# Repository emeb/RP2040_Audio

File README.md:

# RP2040_Audio
A Eurorack module for stereo audio effects based on the Raspberry Pi RP2040 MCU

## Abstract
I've been doing audio synthesis and effects in the Eurorack modular market for
a number of years. I started out in the late 2000's using the Microchip dsPIC
and migrated over to ARM Cortex M devices, mostly STM32 in order to get access
to higher speeds, more memory and floating point math. This was my main
platform for most of the 2010's until the great silicon drought of the 2020's
made high-end STM32 devices almost impossible to get. Into the vacuum stepped
the good folks at the Raspberry Pi Foundation with the RP2040 MCU which has
a fair chunk of on-chip SRAM, dual ARM Cortex M0 cores and a decent complement
of peripherals.

This project is a feasibility study of using the RP2040 MCU as an audio effects
processor, with particular emphasis on performance with challenging DSP.

## Hardware
The complete design consists of two PCBs:
* The system PCB - a single board containg all electrical components. Find it
in the Hardware directory.
* The Front Panel - a PCB-based front panel that conforms to the Eurorack
physical mounting standard. Found in the Hardware/audio_panel directory.

The system PCB has the following features:
* Standard Eurorack 16-pin shrouded power connector
* Two +/-5V CV inputs and associated analog signal conditioning 
* Two +/-7V Audio inputs and associated analog signal conditioning 
* Two +/-7V Audio outputs and associated analog drivers
* WM8731 stereo audio codec
* RP2040 and 4MB SPI flash with USB, SWD and serial interfaces for development
* 160 x 80 IPS LCD
* UI button

## Firmware
A demonstration firmware is included that exercises all of the capabilities of
the system, including the LCD, UI button, CV inputs and stereo audio I/O. It is
a basic multi-effects unit that supports a complement of audio DSP algorithms
that are easily extended by adding standardized modules to a data structure.
As provided here just three algorithms are available:
* Simple pass-thru with no processing
* Simple gain control
* Basic "clean delay" with crossfaded deglitching during delay changes.

Other algorithms have been tested including phasers, flangers, frequency shifters,
resampling delays and reverbs, but these are not publicly released at this time.

## Findings
Overall the RP2040 is a capable device that can do a reasonable amount of audio
DSP. The lack of floating point is not a huge incovenience if one is handy with
fixed point arithmetic and the large on-chip SRAM is sufficiently large for
reasonable audio data buffers. The PIO is handy for building interfaces and is
capable of full-duplex I2S with no difficulty. The on-chip ADC underperforms its
12-bit data width however and requires a fair bit of post-processing to remove
noise and jitter in the conversion results. The dual ARM cores are useful in
dividing up user interface and DSP tasks to keep a snappy response, but even
with two cores the system struggles to compete with higher-spec ARM systems.

TL;DR - you can use it for DSP, but I'd prefer a Cortex M7.

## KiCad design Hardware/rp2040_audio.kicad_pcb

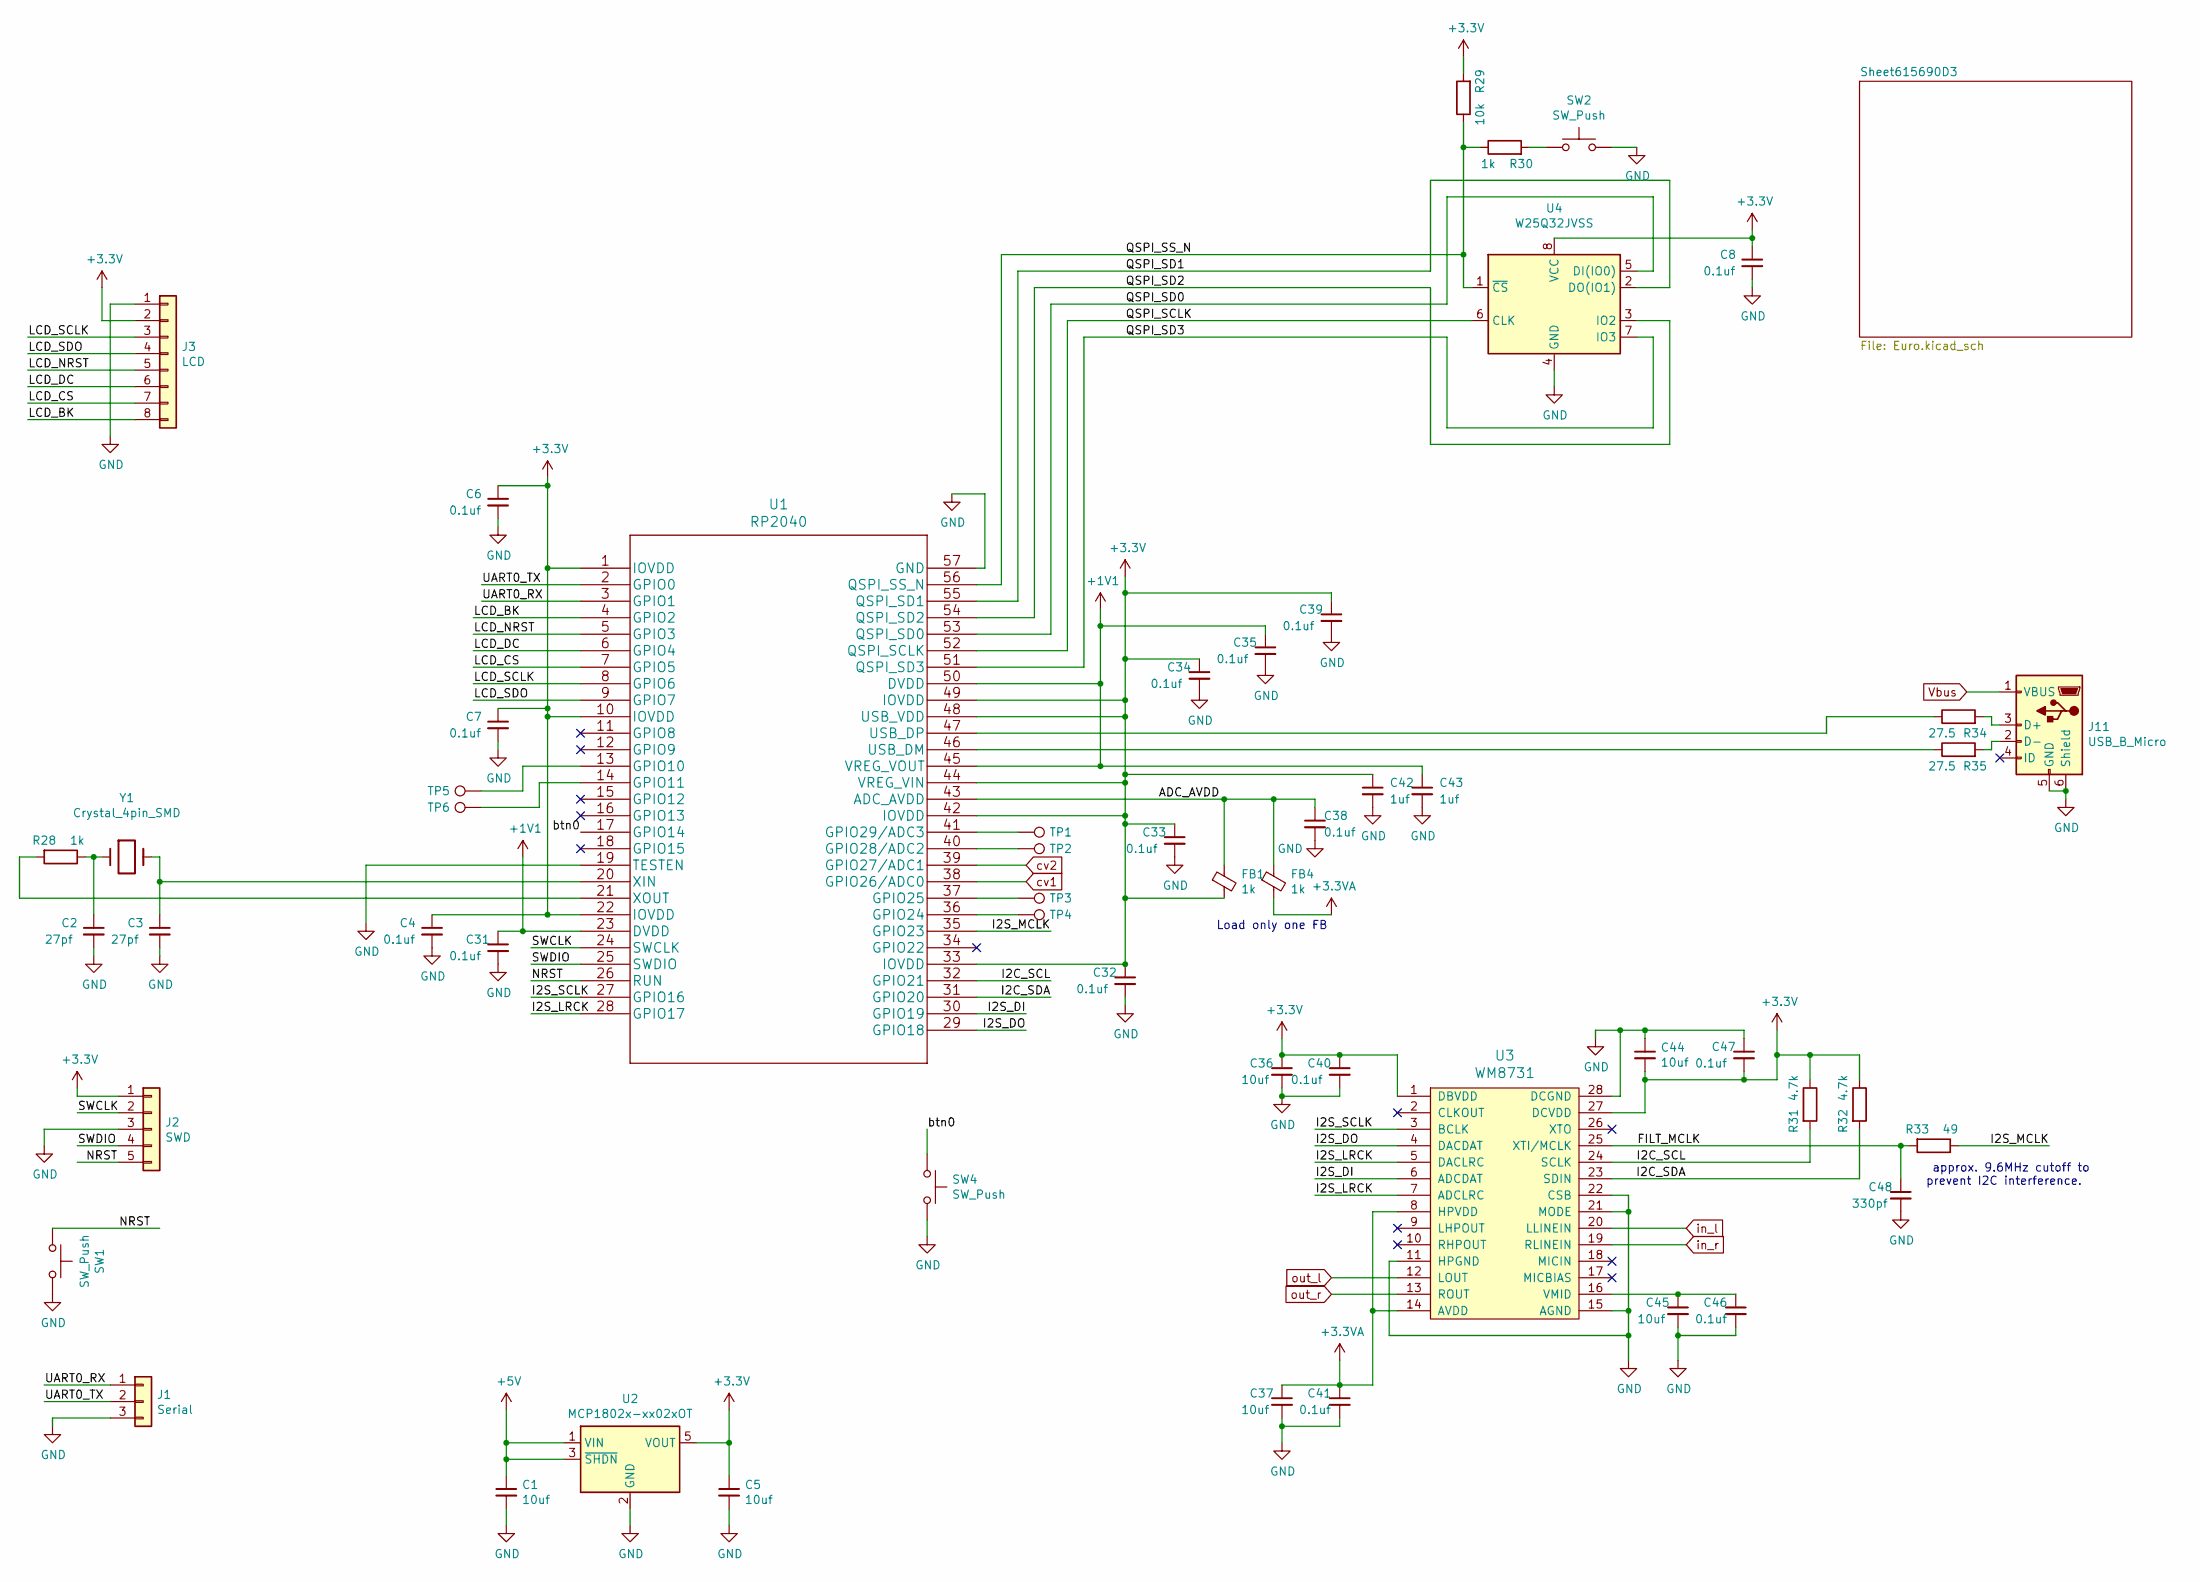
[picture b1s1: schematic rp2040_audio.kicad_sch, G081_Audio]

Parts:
C1, C5, C36, C37, C44, C45: 10uf; C_0805
C2, C3: 27pf; C_0603
C4, C6, C7, C8, C31, C32, C33, C34, C35, C38, C39, C40, C41, C46, C47: 0.1uf; C_0603
C42, C43: 1uf; C_0603
C48: 330pf; C_0603
FB1, FB4: 1k; C_0603
J1: Serial; Pin_Header_Straight_1x03_Pitch2.54mm
J2: SWD; Pin_Header_Straight_1x05_Pitch2.54mm
J3: LCD; LCD_80x160_0.96
J11: USB_B_Micro; USB_Micro-B_10103594-0001LF_actual_outline
R28, R30: 1k; R_0603
R29: 10k; R_0603
R31, R32: 4.7k; R_0603
R33: 49; R_0603
R34, R35: 27.5; R_0603
SW1, SW2: SW_Push; SW_SPST_KMR2
SW4: SW_Push; SW_PUSH_6mm_Center
TP1, TP2, TP3, TP4, TP5, TP6: TestPoint; Measurement_Point_Round-SMD-Pad_Small
U1: RP2040
U2: MCP1802x-xx02xOT; SOT-23-5
U3: WM8731; SSOP-28_5.3x10.2mm_Pitch0.65mm
U4: W25Q32JVSS; SOIC-8_5.23x5.23mm_P1.27mm
Y1: Crystal_4pin_SMD; Crystal_SMD_3225-4pin_3.2x2.5mm

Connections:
+1V1: C31.1, C35.1, C43.1, U1.23 (DVDD), U1.45 (VREG_VOUT), U1.50 (DVDD)
+3.3VA: C37.1, C41.1, FB4.2, U3.8 (HPVDD), U3.14 (AVDD); also elsewhere on the board
+3V3: C4.1, C5.1, C6.1, C7.1, C8.1, C32.1, C33.1, C34.1, C36.1, C39.1, C40.1, C42.1, C44.2, C47.2, FB1.2, J2.1, J3.2, R29.2, R31.1, R32.1, U1.1 (IOVDD), U1.10 (IOVDD), U1.22 (IOVDD), U1.33 (IOVDD), U1.42 (IOVDD), U1.44 (VREG_VIN), U1.48 (USB_VDD), U1.49 (IOVDD), U2.5 (VOUT), U3.1 (DBVDD), U3.27 (DCVDD), U4.8 (VCC)
+5V: C1.1, U2.1 (VIN), U2.3 (~SHDN); also elsewhere on the board
/ADC_AVDD: C38.1, FB1.1, FB4.1, U1.43 (ADC_AVDD)
/FILT_MCLK: C48.1, R33.2, U3.25 (XTI/MCLK)
/I2C_SCL: R31.2, U1.32 (GPIO21), U3.24 (SCLK)
/I2C_SDA: R32.2, U1.31 (GPIO20), U3.23 (SDIN)
/I2S_DI: U1.30 (GPIO19), U3.6 (ADCDAT)
/I2S_DO: U1.29 (GPIO18), U3.4 (DACDAT)
/I2S_LRCK: U1.28 (GPIO17), U3.5 (DACLRC), U3.7 (ADCLRC)
/I2S_MCLK: R33.1, U1.35 (GPIO23)
/I2S_SCLK: U1.27 (GPIO16), U3.3 (BCLK)
/LCD_BK: J3.8, U1.4 (GPIO2)
/LCD_CS: J3.7, U1.7 (GPIO5)
/LCD_DC: J3.6, U1.6 (GPIO4)
/LCD_NRST: J3.5, U1.5 (GPIO3)
/LCD_SCLK: J3.3, U1.8 (GPIO6)
/LCD_SDO: J3.4, U1.9 (GPIO7)
/NRST: J2.5, SW1.1, U1.26 (RUN)
/QSPI_SCLK: U1.52 (QSPI_SCLK), U4.6 (CLK)
/QSPI_SD0: U1.53 (QSPI_SD0), U4.5 (DI(IO0))
/QSPI_SD1: U1.55 (QSPI_SD1), U4.2 (DO(IO1))
/QSPI_SD2: U1.54 (QSPI_SD2), U4.3 (IO2)
/QSPI_SD3: U1.51 (QSPI_SD3), U4.7 (IO3)
/QSPI_SS_N: R29.1, R30.1, U1.56 (QSPI_SS_N), U4.1 (~CS)
/SWCLK: J2.2, U1.24 (SWCLK)
/SWDIO: J2.4, U1.25 (SWDIO)
/UART0_RX: J1.1, U1.3 (GPIO1)
/UART0_TX: J1.2, U1.2 (GPIO0)
/btn0: SW4.1, U1.17 (GPIO14)
GND: C1.2, C2.2, C3.2, C4.2, C5.2, C6.2, C7.2, C8.2, C31.2, C32.2, C33.2, C34.2, C35.2, C36.2, C37.2, C38.2, C39.2, C40.2, C41.2, C42.2, C43.2, C44.1, C45.2, C46.2, C47.1, C48.2, J1.3, J2.3, J3.1, J11.5 (GND), J11.6 (Shield), SW1.2, SW2.2, SW4.2, U1.19 (TESTEN), U1.57 (GND), U2.2 (GND), U3.11 (HPGND), U3.15 (AGND), U3.21 (MODE), U3.22 (CSB), U3.28 (DCGND), U4.4 (GND); also elsewhere on the board
unnamed: C2.1, R28.1, Y1.1
unnamed: C3.1, U1.20 (XIN), Y1.3
unnamed: C45.1, C46.1, U3.16 (VMID)
unnamed: J11.2 (D-), R35.2
unnamed: J11.3 (D+), R34.2
unnamed: R28.2, U1.21 (XOUT)
unnamed: R30.2, SW2.1
unnamed: R34.1, U1.47 (USB_DP)
unnamed: R35.1, U1.46 (USB_DM)
unnamed: TP1.1, U1.41 (GPIO29/ADC3)
unnamed: TP2.1, U1.40 (GPIO28/ADC2)
unnamed: TP3.1, U1.37 (GPIO25)
unnamed: TP4.1, U1.36 (GPIO24)
unnamed: TP5.1, U1.13 (GPIO10)
unnamed: TP6.1, U1.14 (GPIO11)
Vbus: J11.1 (VBUS); also elsewhere on the board
cv1: U1.38 (GPIO26/ADC0); also elsewhere on the board
cv2: U1.39 (GPIO27/ADC1); also elsewhere on the board
in_l: U3.20 (LLINEIN); also elsewhere on the board
in_r: U3.19 (RLINEIN); also elsewhere on the board
out_l: U3.12 (LOUT); also elsewhere on the board
out_r: U3.13 (ROUT); also elsewhere on the board

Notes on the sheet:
approx. 9.6MHz cutoff to prevent I2C interference.
Load only one FB

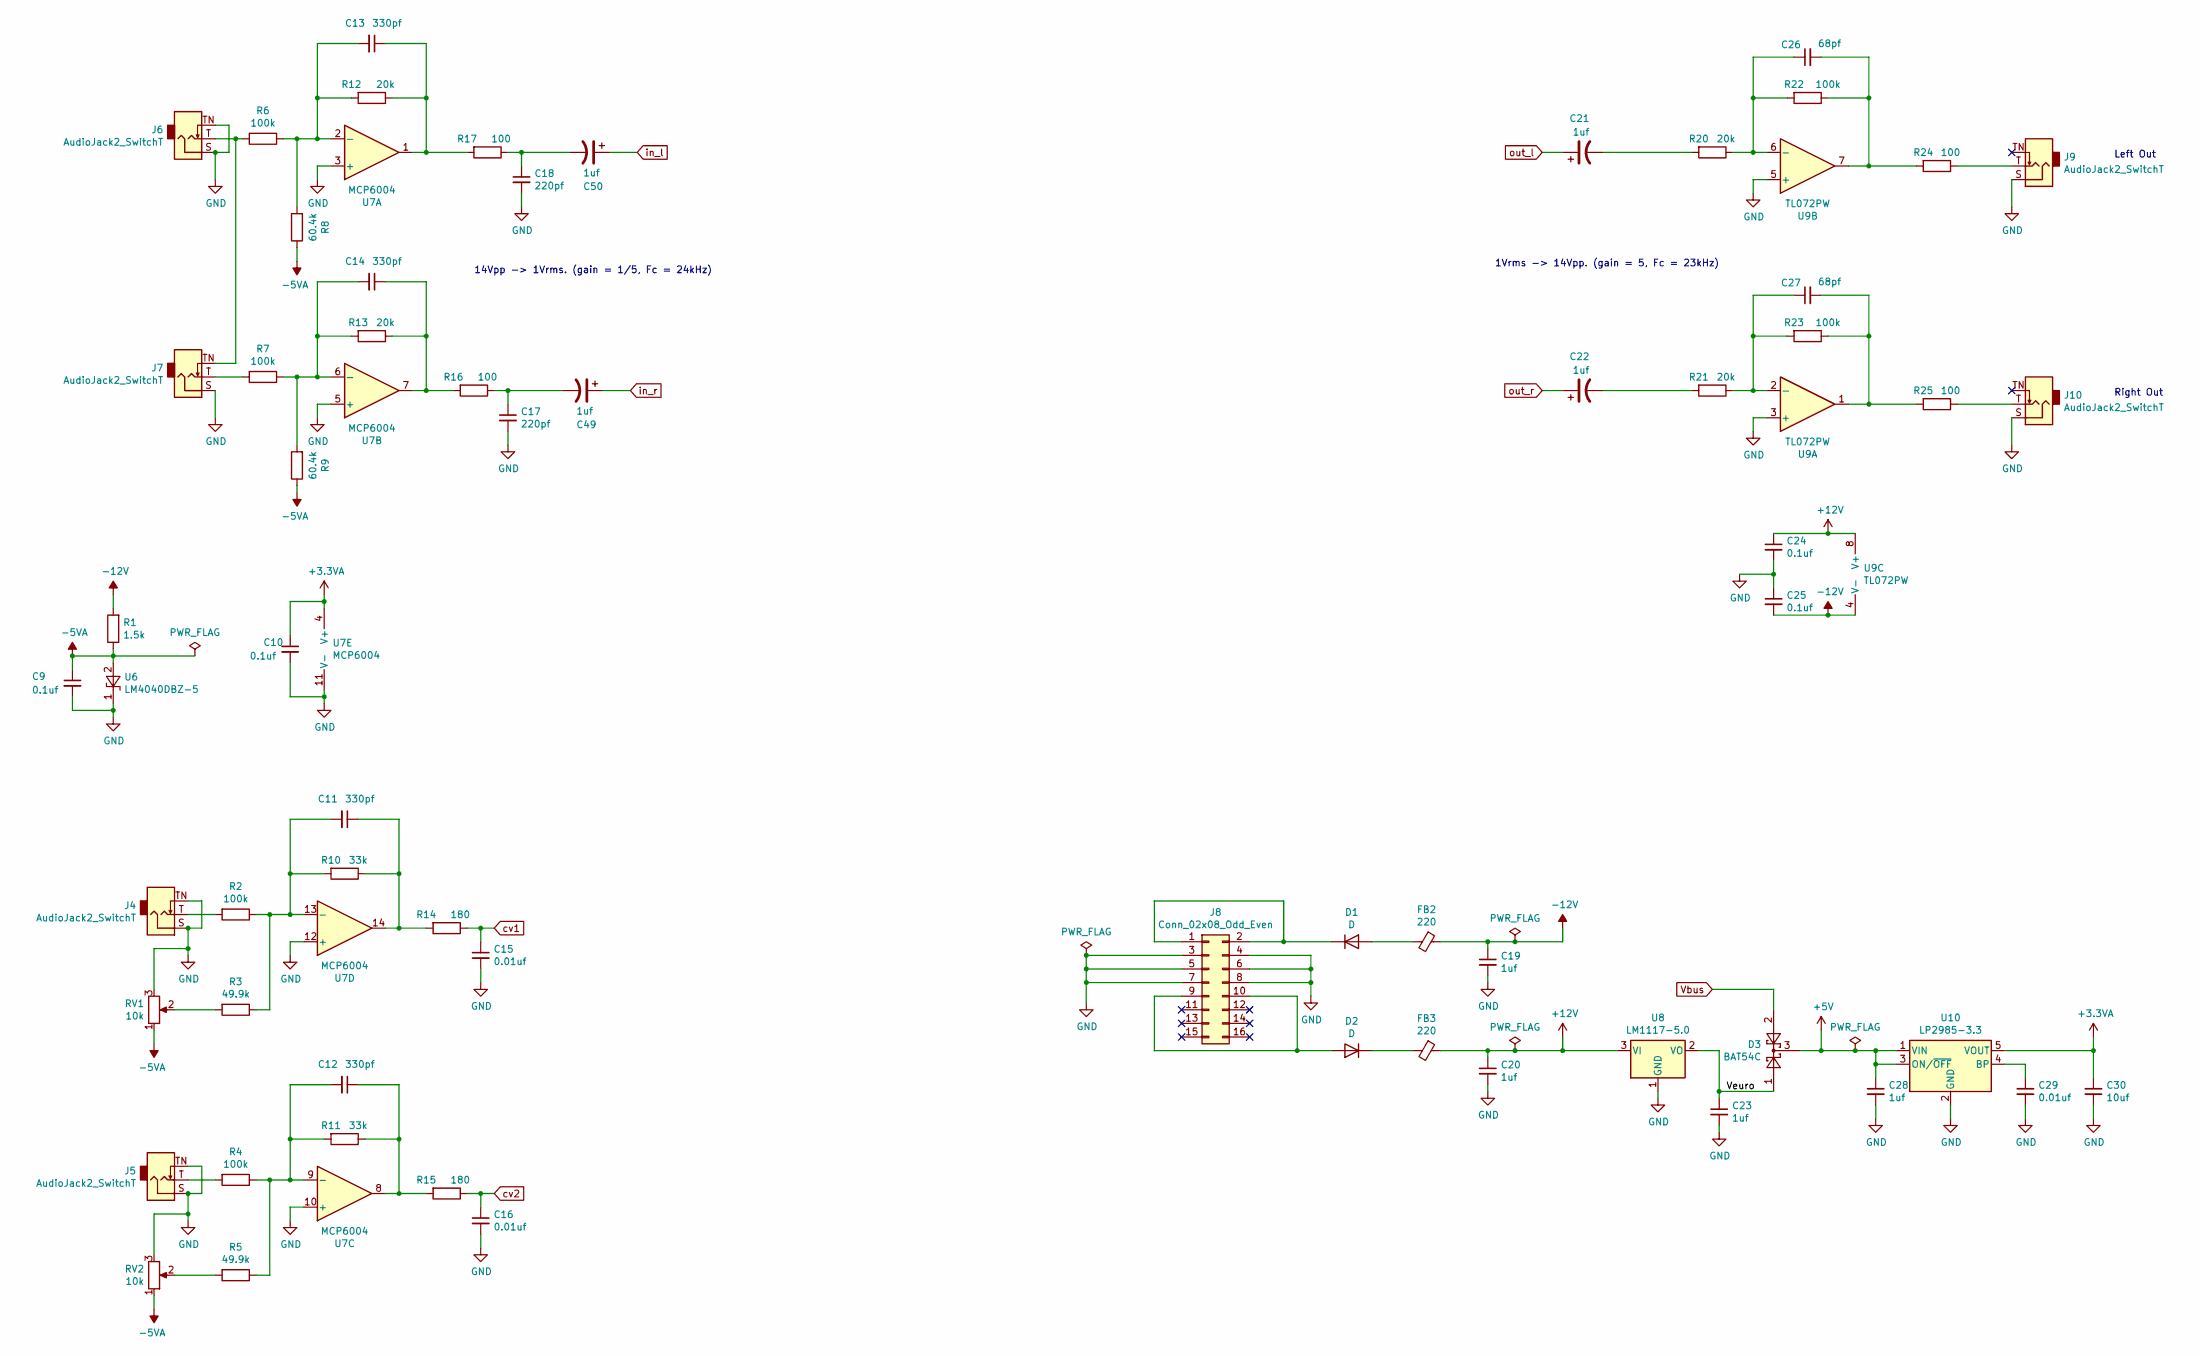
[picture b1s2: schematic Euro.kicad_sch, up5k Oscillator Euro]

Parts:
C9, C10, C24, C25: 0.1uf; C_0603
C11, C12, C13, C14: 330pf; C_0603
C15, C16, C29: 0.01uf; C_0603
C17, C18: 220pf; C_0603
C19, C20, C23, C28: 1uf; C_0603
C21, C22, C49, C50: 1uf; CP_Elec_4x5.3
C26, C27: 68pf; C_0603
C30: 10uf; C_0805
D1, D2: D; D_SMA
D3: BAT54C; SOT-23
FB2, FB3: 220; R_0805
J4, J5, J6, J7, J9, J10: AudioJack2_SwitchT; Jack_3.5mm_QingPu_WQP-PJ398SM_Vertical_CircularHoles
J8: Conn_02x08_Odd_Even; 5103308-3
R1: 1.5k; R_0603
R2, R4, R6, R7, R22, R23: 100k; R_0603
R3, R5: 49.9k; R_0603
R8, R9: 60.4k; R_0603
R10, R11: 33k; R_0603
R12, R13, R20, R21: 20k; R_0603
R14, R15: 180; R_0603
R16, R17, R24, R25: 100; R_0603
RV1, RV2: 10k; Potentiometer_TT_P0915N
U6: LM4040DBZ-5; SOT-23
U7: MCP6004; TSSOP-14_4.4x5mm_Pitch0.65mm
U8: LM1117-5.0; SOT-223-3_TabPin2
U9: TL072PW; TSSOP-8_4.4x3mm_Pitch0.65mm
U10: LP2985-3.3; SOT-23-5

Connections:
+3.3VA: C10.1, C30.1, U7.4 (V+), U10.5 (VOUT); also elsewhere on the board
+5V: C28.1, D3.3, U10.1 (VIN), U10.3 (ON/~OFF); also elsewhere on the board
+12V: C20.1, C24.1, FB3.1, U8.3 (VI), U9.8 (V+)
-5VA: C9.1, R1.1, R8.1, R9.1, RV1.1, RV2.1, U6.2 (A)
-12V: C19.1, C25.2, FB2.1, R1.2, U9.4 (V-)
/Sheet615690D3/Veuro: C23.1, D3.1, U8.2 (VO)
GND: C9.2, C10.2, C15.2, C16.2, C17.2, C18.2, C19.2, C20.2, C23.2, C24.2, C25.1, C28.2, C29.2, C30.2, J4.S, J4.TN, J5.S, J5.TN, J6.S, J6.TN, J7.S, J8.3, J8.4, J8.5, J8.6, J8.7, J8.8, J9.S, J10.S, RV1.3, RV2.3, U6.1 (K), U7.3 (+), U7.5 (+), U7.10 (+), U7.11 (V-), U7.12 (+), U8.1 (GND), U9.3 (+), U9.5 (+), U10.2 (GND); also elsewhere on the board
unnamed: C11.1, R10.1, R14.2, U7.14
unnamed: C11.2, R2.1, R3.1, R10.2, U7.13 (-)
unnamed: C12.1, R11.1, R15.2, U7.8
unnamed: C12.2, R4.1, R5.1, R11.2, U7.9 (-)
unnamed: C13.1, R12.1, R17.2, U7.1
unnamed: C13.2, R6.1, R8.2, R12.2, U7.2 (-)
unnamed: C14.1, R13.1, R16.2, U7.7
unnamed: C14.2, R7.1, R9.2, R13.2, U7.6 (-)
unnamed: C17.1, C49.2, R16.1
unnamed: C18.1, C50.2, R17.1
unnamed: C21.2, R20.2
unnamed: C22.2, R21.2
unnamed: C26.1, R20.1, R22.2, U9.6 (-)
unnamed: C26.2, R22.1, R24.2, U9.7
unnamed: C27.1, R21.1, R23.2, U9.2 (-)
unnamed: C27.2, R23.1, R25.2, U9.1
unnamed: C29.1, U10.4 (BP)
unnamed: D1.1 (K), J8.1, J8.2
unnamed: D1.2 (A), FB2.2
unnamed: D2.1 (K), FB3.2
unnamed: D2.2 (A), J8.9, J8.10
unnamed: J4.T, R2.2
unnamed: J5.T, R4.2
unnamed: J6.T, J7.TN, R6.2
unnamed: J7.T, R7.2
unnamed: J9.T, R24.1
unnamed: J10.T, R25.1
unnamed: R3.2, RV1.2
unnamed: R5.2, RV2.2
Vbus: D3.2; also elsewhere on the board
cv1: C15.1, R14.1; also elsewhere on the board
cv2: C16.1, R15.1; also elsewhere on the board
in_l: C50.1; also elsewhere on the board
in_r: C49.1; also elsewhere on the board
out_l: C21.1; also elsewhere on the board
out_r: C22.1; also elsewhere on the board

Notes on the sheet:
Right Out
14Vpp -> 1Vrms. (gain = 1/5, Fc = 24kHz)
1Vrms -> 14Vpp. (gain = 5, Fc = 23kHz)
Left Out

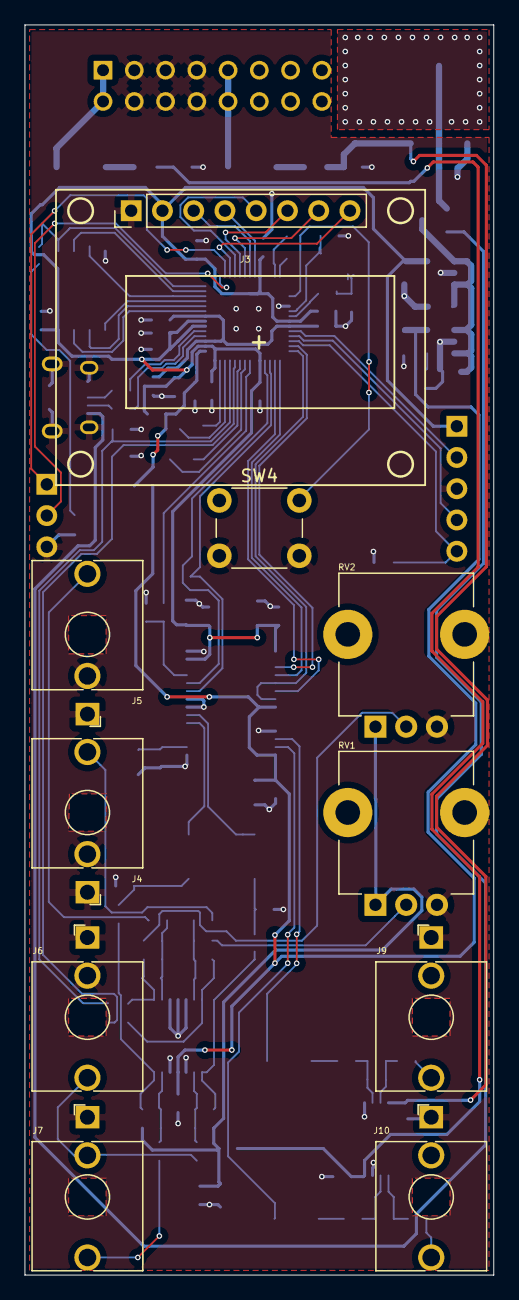
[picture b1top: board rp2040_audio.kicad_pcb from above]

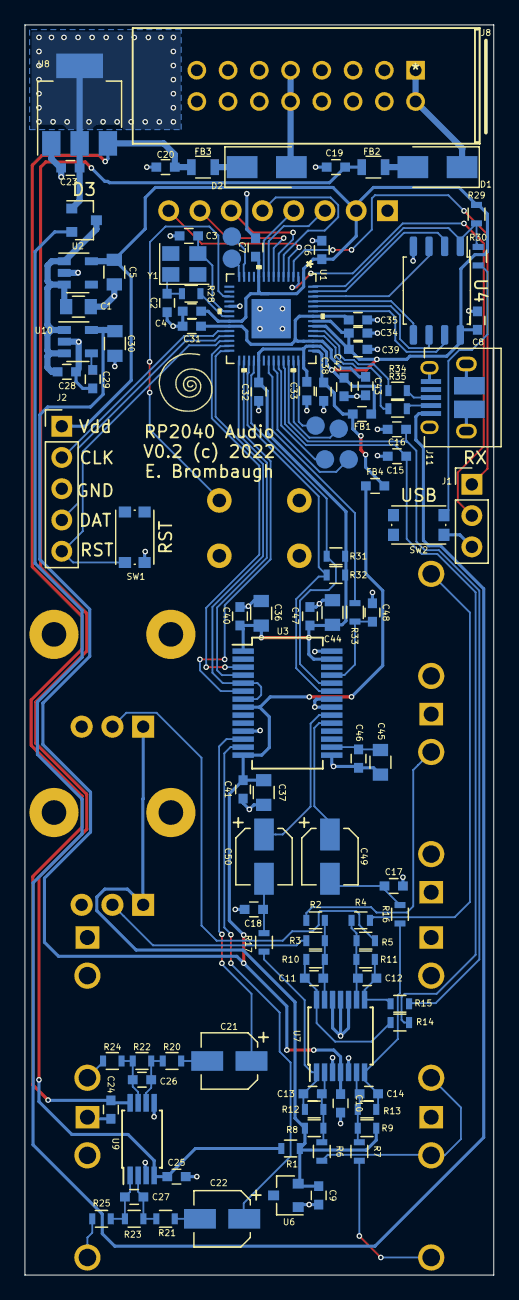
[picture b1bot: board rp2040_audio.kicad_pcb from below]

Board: 2 copper layers, 38.1 x 101.6 mm, 121 parts (111 on the bottom side), 87 nets.

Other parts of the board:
Ref**: Val**; avatar_small

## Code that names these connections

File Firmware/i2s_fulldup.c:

/*
 * i2s_fulldup.c - PIO-based full-duplex I2S for RP2040
 * 12-19-21 E. Brombaugh
 *
 * Based on original ideas from
 * https://gist.github.com/jonbro/3da573315f066be8ea390db39256f9a7
 * and the pico-extras library.
 */

#include <stdio.h>
#include <string.h>
#include "i2s_fulldup.h"
#include "hardware/dma.h"
#include "hardware/irq.h"
#include "hardware/pio.h"
#include "hardware/structs/clocks.h"
#include "hardware/clocks.h"
#include "pico/multicore.h"
#include "i2s_fulldup.pio.h"
#include "audio.h"

/* uncomment this to run audio processing on core 1 */
#define MULTICORE

/* I2S PIO has L+R (Frames) in 32-bits */
#define FRAMES_PER_BUFFER (BUFSZ/2)

/* I2S comes out on these pins */
#if 0
/* HW V0.1 */
#define I2S_DO_PIN 18		// data out
#define I2S_DI_PIN 17		// data in
#define I2S_CLK_PIN_BASE 24	// BCLK, LRCK (Temporarily on TP3, TP4)
#define I2S_MCLK_PIN 23		// MCLK

#define IN_DIAG_PIN 10		// TP5
#define OUT_DIAG_PIN 11		// TP6
#else
/* HW V0.2 */
#define I2S_DO_PIN 18		// data out
#define I2S_DI_PIN 19		// data in
#define I2S_CLK_PIN_BASE 16	// BCLK, LRCK
#define I2S_MCLK_PIN 23		// MCLK

#define IN_DIAG_PIN 10		// TP5
#define OUT_DIAG_PIN 11		// TP6
#endif

/* resources we use */
PIO pio;
uint sm;
uint dma_chan_input, dma_chan_output;
uint ib_idx, ob_idx;
uint32_t input_buf[2*FRAMES_PER_BUFFER], output_buf[2*FRAMES_PER_BUFFER],
	xfer_buf[FRAMES_PER_BUFFER];

/*
 * IRQ0 handler - used only for I2S input
 * ATM this is not double-buffered, but it would be prudent to
 * do so if adding code to compute the next buffer.
 */
void dma_input_handler(void)
{
	gpio_put(IN_DIAG_PIN, 1);
	
	/* Clear IRQ for I2S input */
    dma_irqn_acknowledge_channel(DMA_IRQ_0, dma_chan_input);
	
	/* reset write address to start of next buffer */
	ib_idx ^= 1;
	dma_channel_set_write_addr(dma_chan_input,
		&input_buf[ib_idx*FRAMES_PER_BUFFER],
		true
	);
	
	/* start next transfer sequence */
	dma_channel_start(dma_chan_input);
	
#if 0
	/* save previous buffer */
	memcpy(xfer_buf, &input_buf[ib_idx*FRAMES_PER_BUFFER],
		FRAMES_PER_BUFFER*sizeof(uint32_t));
#else
	/* do audio processing on previous buffer */
	Audio_Proc((int16_t *)xfer_buf,
	(int16_t *)&input_buf[(ib_idx^1)*FRAMES_PER_BUFFER],
		2*FRAMES_PER_BUFFER);
#endif

	gpio_put(IN_DIAG_PIN, 0);
}

/*
 * IRQ1 handler - used only for I2S output
 * ATM this is not double-buffered, but it would be prudent to
 * do so if adding code to compute the next buffer.
 */
void dma_output_handler()
{
	gpio_put(OUT_DIAG_PIN, 1);
	
	/* Clear IRQ for I2S output */
    dma_irqn_acknowledge_channel(DMA_IRQ_1, dma_chan_output);
	
	/* reset read address to start of next buffer */
	ob_idx ^= 1;
	dma_channel_set_read_addr(dma_chan_output,
		&output_buf[ob_idx*FRAMES_PER_BUFFER],
		true
	);
	
	/* start next transfer sequence */
	dma_channel_start(dma_chan_output);
	
	/* fill previous buffer with new data */
#if 1
	/* loopback */
	memcpy(&output_buf[ob_idx*FRAMES_PER_BUFFER], xfer_buf,
		FRAMES_PER_BUFFER*sizeof(uint32_t));
#else
	/* do audio processing */
	Audio_Proc((int16_t *)&output_buf[ob_idx*FRAMES_PER_BUFFER],
		(int16_t *)xfer_buf,
		2*FRAMES_PER_BUFFER);
#endif
	
	gpio_put(OUT_DIAG_PIN, 0);
}

#ifdef MULTICORE
/*
 * entry point for 2nd core to start running
 */
void core1_entry()
{
	/* enable IRQ handler for dma input */
    irq_set_exclusive_handler(DMA_IRQ_0, dma_input_handler);
    irq_set_enabled(DMA_IRQ_0, true);
	

	/* enable IRQ handler for dma output */
    irq_set_exclusive_handler(DMA_IRQ_1, dma_output_handler);
    irq_set_enabled(DMA_IRQ_1, true);
	
	/* enable multicore lockout */
	multicore_lockout_victim_init();

	/* loop here waiting for IRQs */
	while(1)
	{
		Audio_Fore();
	}
}
#endif

/*
 * initialize the I2S processing
 */
void init_i2s_fulldup(void)
{
	int32_t i;
	int16_t *obuf = (int16_t *)output_buf;
	int16_t *ibuf = (int16_t *)input_buf;
	
	/* clear buffers */
	for(i=0;i<2*FRAMES_PER_BUFFER;i++)
	{
		*ibuf++ = 0;
		*ibuf++ = 0;
		*obuf++ = 0;
		*obuf++ = 0;
	}

	/* diag GPIO */
	gpio_init(IN_DIAG_PIN);
	gpio_set_dir(IN_DIAG_PIN, GPIO_OUT);
	gpio_init(OUT_DIAG_PIN);
	gpio_set_dir(OUT_DIAG_PIN, GPIO_OUT);

    /* set up PIO */
    pio = pio0;
    uint offset = pio_add_program(pio, &i2s_fulldup_program);
    printf("loaded program at offset: %i\n", offset);
    sm = pio_claim_unused_sm(pio, true);
    printf("claimed sm: %i\n", sm);
	
	/* compute PIO divider for desired sample rate */
    uint32_t system_clock_frequency = clock_get_hz(clk_sys);
    assert(system_clock_frequency < 0x40000000);
    printf("System clock %u Hz\n", (uint) system_clock_frequency);
    uint32_t sample_freq = 48000;
    printf("Target sample freq %d\n", sample_freq);
    uint32_t divider = system_clock_frequency * 2 / sample_freq; // avoid arithmetic overflow
    divider = divider & ~(0x1ff); // mask off bottom 9 for exact MCLK/BCLK ratio of 4.0
    assert(divider < 0x1000000);
    printf("PIO clock divider 0x%x/256\n", divider);
	printf("Actual sample freq = %d\n", 2 * system_clock_frequency / divider);
	
	/* set up the PIO and divider */
    i2s_fulldup_program_init(
		pio,
		sm,
		offset,
		I2S_DO_PIN,
		I2S_DI_PIN,
		I2S_CLK_PIN_BASE
	);
    pio_sm_set_clkdiv_int_frac(pio, sm, divider >> 8u, divider & 0xffu);
	
	/* generate an MCLK on GPIO at 8x BCLK (256x LRCK) */
	gpio_set_function(I2S_MCLK_PIN, GPIO_FUNC_GPCK);
	clock_gpio_init(I2S_MCLK_PIN, CLOCKS_CLK_GPOUT1_CTRL_AUXSRC_VALUE_CLK_SYS, divider>>9);
	printf("MCLK at %d Hz\n", system_clock_frequency/(divider>>9));
	
    /* configure dma channel for input */
	ib_idx = 0;
    dma_chan_input = dma_claim_unused_channel(true);
	printf("DMA input using chl %d\n", dma_chan_input);
    dma_channel_config c = dma_channel_get_default_config(dma_chan_input);
    channel_config_set_read_increment(&c,false);
    channel_config_set_write_increment(&c,true);
    channel_config_set_dreq(&c,pio_get_dreq(pio,sm,false));
    channel_config_set_transfer_data_size(&c, DMA_SIZE_32);

    dma_channel_configure(
        dma_chan_input,
        &c,
        input_buf, 			// Destination pointer
        &pio->rxf[sm], 		// Source pointer
        FRAMES_PER_BUFFER, // Number of transfers
        true				// Start immediately
    );
    dma_channel_set_irq0_enabled(dma_chan_input, true);

    /* configure dma channel for output */
	ob_idx = 0;
	dma_chan_output = dma_claim_unused_channel(true);
	printf("DMA output using chl %d\n", dma_chan_output);
    dma_channel_config cc = dma_channel_get_default_config(dma_chan_output);
    channel_config_set_read_increment(&cc,true);
    channel_config_set_write_increment(&cc,false);
    channel_config_set_dreq(&cc,pio_get_dreq(pio,sm,true));
    channel_config_set_transfer_data_size(&cc, DMA_SIZE_32);
    dma_channel_configure(
        dma_chan_output,
        &cc,
        &pio->txf[sm],		// Destination pointer
        output_buf,			// Source pointer
        FRAMES_PER_BUFFER,	// Number of transfers
        true				// Start immediately
    );
    dma_channel_set_irq1_enabled(dma_chan_output, true);
    
#ifndef MULTICORE
	/* No multi-core - just use core 0 */
	
	/* enable IRQ handler for dma input */
    irq_set_exclusive_handler(DMA_IRQ_0, dma_input_handler);
    irq_set_enabled(DMA_IRQ_0, true);

	/* enable IRQ handler for dma output */
    irq_set_exclusive_handler(DMA_IRQ_1, dma_output_handler);
    irq_set_enabled(DMA_IRQ_1, true);
	
	printf("Single core background started\n");
#else
	/* multi-core operation */
	multicore_launch_core1(core1_entry);
	printf("Multicore background started\n");
#endif

	/* Start PIO */
    pio_sm_set_enabled(pio, sm, true);
	printf("PIO started\n");
}

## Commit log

2022-04-11 Initial commit of RP2040 project
2022-04-11 Working on formatting
2022-04-11 more formatting
2022-04-11 Get build working, add docs
2022-04-11 shell formatting
2022-04-11 Add credit
2022-04-11 Remove unused stuff from list

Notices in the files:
Hardware/rp2040_audio.kicad_pcb:
V0.2 (c) 2022
parts and their libraries:
Copyright 2016 Accelerated Designs. All rights reserved.
Copyright 2021 Accelerated Designs. All rights reserved.
